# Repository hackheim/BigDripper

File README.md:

# Big Dripper 

### BigDripper – Controller Board and Operating Principle

BigDripper is Hackheim’s version of the classic bicycle-mounted water printer (see links below). The printer is being developed as a community project, with the goal of having it completed by the end of September 2026.

The printer consists of 16 solenoid valves mounted in a row across the bicycle trailer. The valves are supplied with water from a tank and pump. When a valve is opened briefly, it releases a small amount of water onto the ground, forming a single pixel. Together, the 16 valves produce one vertical column of 16 pixels. As the bicycle moves forward and new columns are printed in sequence, the trailer effectively operates as a large-scale dot-matrix printer.

An encoder measures the distance travelled by the bicycle. Rather than advancing through the image at fixed time intervals, the controller selects the next column after the bicycle has travelled a predefined distance. This helps maintain the proportions of the printed text or graphics even when the cycling speed varies.

### Controller board

The controller is based on an ESP32-S3 DevKitC-1, which plugs into a custom-designed carrier board. To make the board easy to maintain and repair—and also suitable for educational use and soldering workshops—we have chosen to use through-hole components throughout the carrier board.

The board has a nominal input voltage of 12 V, which is also the operating voltage of the solenoid valves. A TL2575-based switching regulator generates 5 V for the ESP32 development board and the other logic circuitry.

The regulator itself supports an input voltage of up to 40 V. However, the input voltage is also supplied directly to the solenoid valves. When using a voltage higher than 12 V, both the valves and all other components connected to the input-voltage rail must therefore be rated for the selected voltage.

### Solenoid valve control

The 16 valve outputs are controlled by IRL540N MOSFETs in a low-side switching configuration. The control signals from the ESP32 use 3.3 V logic and are therefore routed through SN74HCT125NE4 buffers powered from 5 V. These buffers provide logic-level translation and drive the MOSFET gates at a higher and more suitable voltage.

Each MOSFET gate is connected to its buffer output through a 33-ohm series resistor. The control signals also have 47-kilohm pull-down resistors, ensuring that the valves remain switched off while the ESP32 is starting, being reset, or not actively driving the outputs.

Each valve output is protected by a dedicated 1N4007 flyback diode. The diode suppresses the inductive voltage spike generated when the current through the solenoid coil is interrupted, protecting the MOSFET from excessive drain voltage.

### Connections and expansion options

The board has a dedicated input for an encoder with transistor outputs and A/B signals. An additional header provides access to 12 spare GPIO signals, together with 3.3 V, 5 V, and ground connections.

Four separate outputs are available for NeoPixel LEDs. These signals are also level-shifted from 3.3 V to 5 V using an SN74HCT125 buffer, and each data output includes a 330-ohm series resistor.

The board also includes indicator LEDs for the 12 V, 5 V, and 3.3 V supply rails, making it easy to verify that the different supply voltages are present.

All external inputs and outputs use WAGO board-to-wire lever connectors, allowing wires to be connected and removed easily without tools.

### Schematic

[schematic](./hardware/pdf/schematic.pdf)

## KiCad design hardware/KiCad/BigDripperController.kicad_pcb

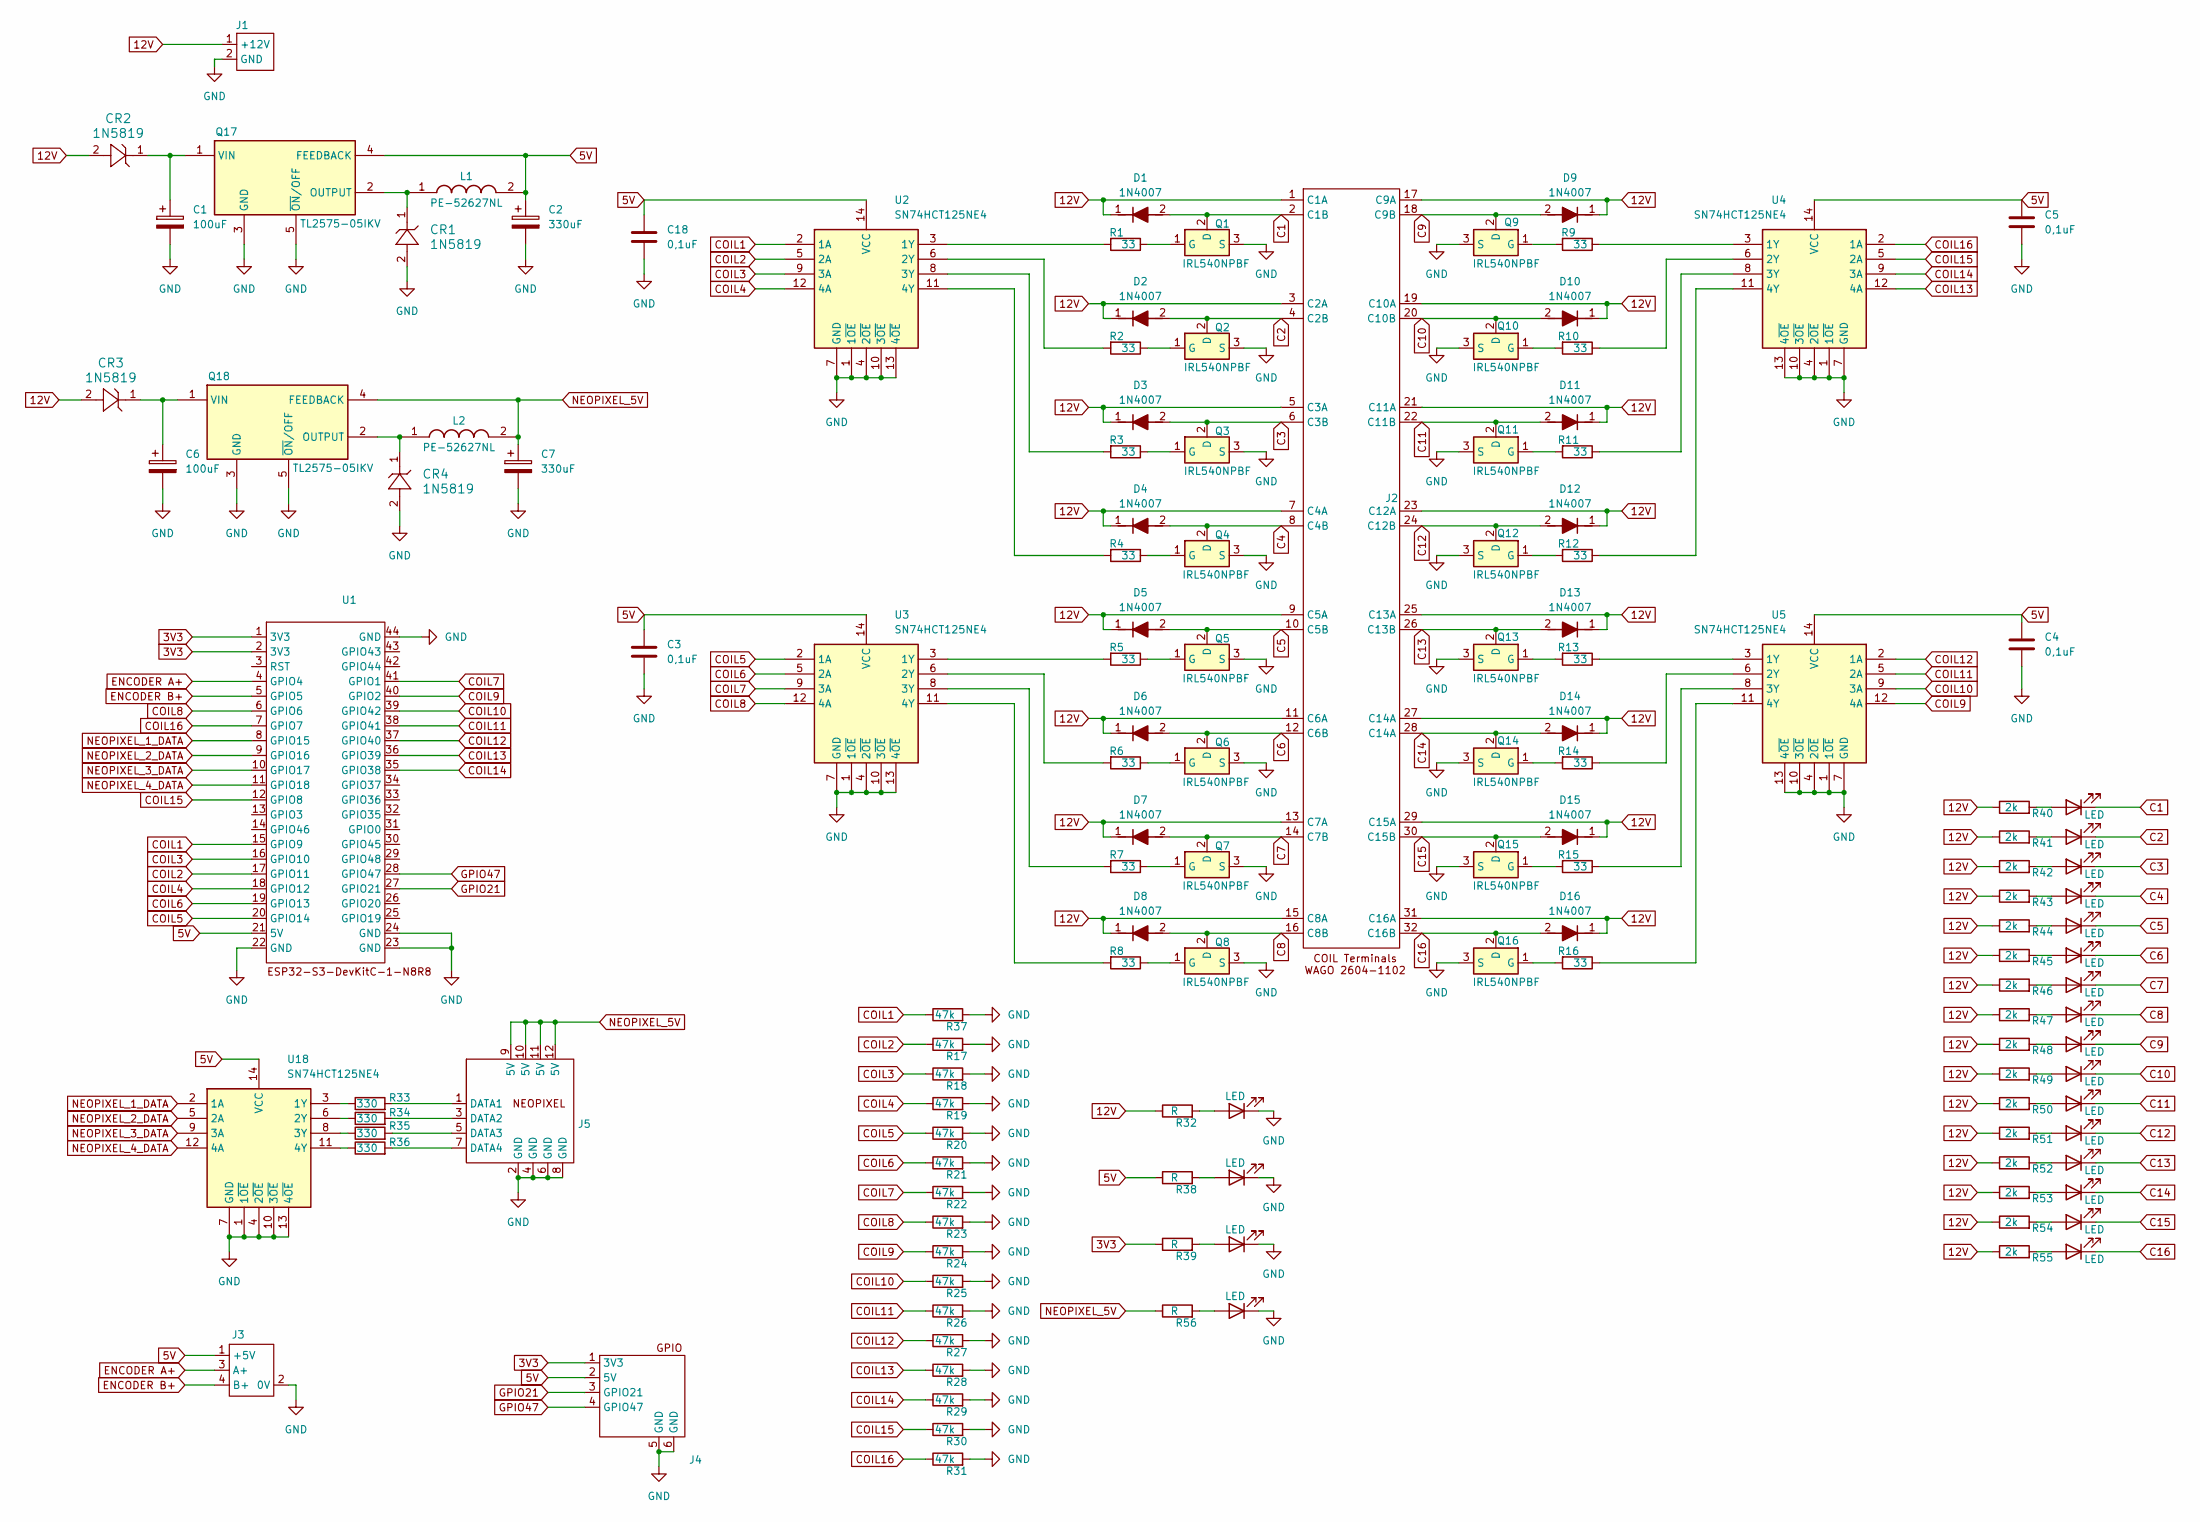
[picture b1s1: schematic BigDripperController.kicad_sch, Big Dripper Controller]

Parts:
C1, C6: 100uF; CAP ALUM 10UF 20% 25V RADIAL TH - WÜRTH - 860020472003
C2, C7: 330uF; CAP ALUM 10UF 20% 25V RADIAL TH - WÜRTH - 860020472003
C3, C4, C5, C18: 0,1uF; CAP0,1uF_K104K15X7RF5TH5V
CR1, CR2, CR3, CR4: 1N5819; DO-41_STM
D1, D2, D3, D4, D5, D6, D7, D8, D9, D10, D11, D12, D13, D14, D15, D16: 1N4007; Mouser Part Number 637-1N4007
D17, D18, D19, D20, D21, D22, D23, D24, D25, D26, D27, D28, D29, D30, D31, D32, D33, D34, D35, D36: LED; LED_D5.0mm
J1: BigDripperPowerConnector-WAGO2604-1102
J2: BigDripperCoilConnector-WAGO2604-1102
J3: BigDripperEncoderConnector-WAGO2604-1102
J4: BigDripperGPIOConnector-WAGO2604-1102
J5: BigDripperNeopixelConnector-WAGO2604-1102
L1, L2: PE-52627NL; PE52627NL; Mouser Part Number 673-PE-52627NL
Q1, Q2, Q3, Q4, Q5, Q6, Q7, Q8, Q9, Q10, Q11, Q12, Q13, Q14, Q15, Q16: IRL540NPBF; Mouser Part Number 942-IRL540NPBF
Q17, Q18: TL2575-05IKV; Mouser Part Number 595-TL2575-05IKV
R1, R2, R3, R4, R5, R6, R7, R8, R9, R10, R11, R12, R13, R14, R15, R16: 33; R_Axial_DIN0207_L6.3mm_D2.5mm_P10.16mm_Horizontal
R17, R18, R19, R20, R21, R22, R23, R24, R25, R26, R27, R28, R29, R30, R31, R37: 47k; R_Axial_DIN0207_L6.3mm_D2.5mm_P10.16mm_Horizontal
R32, R38, R39, R56: R; R_Axial_DIN0207_L6.3mm_D2.5mm_P10.16mm_Horizontal
R33, R34, R35, R36: 330; R_Axial_DIN0207_L6.3mm_D2.5mm_P10.16mm_Horizontal
R40, R41, R42, R43, R44, R45, R46, R47, R48, R49, R50, R51, R52, R53, R54, R55: 2k; R_Axial_DIN0207_L6.3mm_D2.5mm_P10.16mm_Horizontal
U1: ESP32-S3-DevKitC-1-N8R8
U2, U3, U4, U5, U18: SN74HCT125NE4; DIP14; Mouser Part Number 595-SN74HCT125NE4

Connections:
3V3: J4.1 (3V3), R39.1, U1.1 (3V3), U1.2 (3V3)
5V: C2.1, C3.1, C4.1, C5.1, C18.1, J3.1 (+5V), J4.2 (5V), L1.2 (1-), Q17.4 (FEEDBACK), R38.1, U1.21 (5V), U2.14 (VCC), U3.14 (VCC), U4.14 (VCC), U5.14 (VCC), U18.14 (VCC)
12V: CR2.2, CR3.2, D1.1 (K), D2.1 (K), D3.1 (K), D4.1 (K), D5.1 (K), D6.1 (K), D7.1 (K), D8.1 (K), D9.1 (K), D10.1 (K), D11.1 (K), D12.1 (K), D13.1 (K), D14.1 (K), D15.1 (K), D16.1 (K), J1.1 (+12V), J2.1 (C1A), J2.3 (C2A), J2.5 (C3A), J2.7 (C4A), J2.9 (C5A), J2.11 (C6A), J2.13 (C7A), J2.15 (C8A), J2.17 (C9A), J2.19 (C10A), J2.21 (C11A), J2.23 (C12A), J2.25 (C13A), J2.27 (C14A), J2.29 (C15A), J2.31 (C16A), R32.1, R40.1, R41.1, R42.1, R43.1, R44.1, R45.1, R46.1, R47.1, R48.1, R49.1, R50.1, R51.1, R52.1, R53.1, R54.1, R55.1
C1: D1.2 (A), D20.1 (K), J2.2 (C1B), Q1.2 (D)
C2: D2.2 (A), D21.1 (K), J2.4 (C2B), Q2.2 (D)
C3: D3.2 (A), D22.1 (K), J2.6 (C3B), Q3.2 (D)
C4: D4.2 (A), D23.1 (K), J2.8 (C4B), Q4.2 (D)
C5: D5.2 (A), D24.1 (K), J2.10 (C5B), Q5.2 (D)
C6: D6.2 (A), D25.1 (K), J2.12 (C6B), Q6.2 (D)
C7: D7.2 (A), D26.1 (K), J2.14 (C7B), Q7.2 (D)
C8: D8.2 (A), D27.1 (K), J2.16 (C8B), Q8.2 (D)
C9: D9.2 (A), D28.1 (K), J2.18 (C9B), Q9.2 (D)
C10: D10.2 (A), D29.1 (K), J2.20 (C10B), Q10.2 (D)
C11: D11.2 (A), D30.1 (K), J2.22 (C11B), Q11.2 (D)
C12: D12.2 (A), D31.1 (K), J2.24 (C12B), Q12.2 (D)
C13: D13.2 (A), D32.1 (K), J2.26 (C13B), Q13.2 (D)
C14: D14.2 (A), D33.1 (K), J2.28 (C14A), Q14.2 (D)
C15: D15.2 (A), D34.1 (K), J2.30 (C15B), Q15.2 (D)
C16: D16.2 (A), D35.1 (K), J2.32 (C16B), Q16.2 (D)
COIL1: R37.1, U1.15 (GPIO9), U2.2 (1A)
COIL2: R17.1, U1.17 (GPIO11), U2.5 (2A)
COIL3: R18.1, U1.16 (GPIO10), U2.9 (3A)
COIL4: R19.1, U1.18 (GPIO12), U2.12 (4A)
COIL5: R20.1, U1.20 (GPIO14), U3.2 (1A)
COIL6: R21.1, U1.19 (GPIO13), U3.5 (2A)
COIL7: R22.1, U1.41 (GPIO1), U3.9 (3A)
COIL8: R23.1, U1.6 (GPIO6), U3.12 (4A)
COIL9: R24.1, U1.40 (GPIO2), U5.12 (4A)
COIL10: R25.1, U1.39 (GPIO42), U5.9 (3A)
COIL11: R26.1, U1.38 (GPIO41), U5.5 (2A)
COIL12: R27.1, U1.37 (GPIO40), U5.2 (1A)
COIL13: R28.1, U1.36 (GPIO39), U4.12 (4A)
COIL14: R29.1, U1.35 (GPIO38), U4.9 (3A)
COIL15: R30.1, U1.12 (GPIO8), U4.5 (2A)
COIL16: R31.1, U1.7 (GPIO7), U4.2 (1A)
ENCODER A+: J3.3 (A+), U1.4 (GPIO4)
ENCODER B+: J3.4 (B+), U1.5 (GPIO5)
GND: C1.2, C2.2, C3.2, C4.2, C5.2, C6.2, C7.2, C18.2, CR1.2, CR4.2, D17.1 (K), D18.1 (K), D19.1 (K), D36.1 (K), J1.2 (GND), J3.2 (0V), J4.5 (GND), J4.6 (GND), J5.2 (GND), J5.4 (GND), J5.6 (GND), J5.8 (GND), Q1.3 (S), Q2.3 (S), Q3.3 (S), Q4.3 (S), Q5.3 (S), Q6.3 (S), Q7.3 (S), Q8.3 (S), Q9.3 (S), Q10.3 (S), Q11.3 (S), Q12.3 (S), Q13.3 (S), Q14.3 (S), Q15.3 (S), Q16.3 (S), Q17.3 (GND), Q17.5 (~ON/OFF), Q18.3 (GND), Q18.5 (~ON/OFF), R17.2, R18.2, R19.2, R20.2, R21.2, R22.2, R23.2, R24.2, R25.2, R26.2, R27.2, R28.2, R29.2, R30.2, R31.2, R37.2, U1.22 (GND), U1.23 (GND), U1.24 (GND), U1.44 (GND), U2.1 (1~OE), U2.4 (2~OE), U2.7 (GND), U2.10 (3~OE), U2.13 (4~OE), U3.1 (1~OE), U3.4 (2~OE), U3.7 (GND), U3.10 (3~OE), U3.13 (4~OE), U4.1 (1~OE), U4.4 (2~OE), U4.7 (GND), U4.10 (3~OE), U4.13 (4~OE), U5.1 (1~OE), U5.4 (2~OE), U5.7 (GND), U5.10 (3~OE), U5.13 (4~OE), U18.1 (1~OE), U18.4 (2~OE), U18.7 (GND), U18.10 (3~OE), U18.13 (4~OE)
GPIO21: J4.3 (GPIO21), U1.27 (GPIO21)
GPIO47: J4.4 (GPIO47), U1.28 (GPIO47)
NEOPIXEL_1_DATA: U1.8 (GPIO15), U18.2 (1A)
NEOPIXEL_2_DATA: U1.9 (GPIO16), U18.5 (2A)
NEOPIXEL_3_DATA: U1.10 (GPIO17), U18.9 (3A)
NEOPIXEL_4_DATA: U1.11 (GPIO18), U18.12 (4A)
NEOPIXEL_5V: C7.1, J5.9 (5V), J5.10 (5V), J5.11 (5V), J5.12 (5V), L2.2 (1-), Q18.4 (FEEDBACK), R56.1
unnamed: D17.2 (A), R32.2
unnamed: D18.2 (A), R38.2
unnamed: D19.2 (A), R39.2
unnamed: D20.2 (A), R40.2
unnamed: D21.2 (A), R41.2
unnamed: D22.2 (A), R42.2
unnamed: D23.2 (A), R43.2
unnamed: D24.2 (A), R44.2
unnamed: D25.2 (A), R45.2
unnamed: D26.2 (A), R46.2
unnamed: D27.2 (A), R47.2
unnamed: D28.2 (A), R48.2
unnamed: D29.2 (A), R49.2
unnamed: D30.2 (A), R50.2
unnamed: D31.2 (A), R51.2
unnamed: D32.2 (A), R52.2
unnamed: D33.2 (A), R53.2
unnamed: D34.2 (A), R54.2
unnamed: D35.2 (A), R55.2
unnamed: D36.2 (A), R56.2
unnamed: J5.1 (DATA1), R33.2
unnamed: J5.3 (DATA2), R34.2
unnamed: J5.5 (DATA3), R35.2
unnamed: J5.7 (DATA4), R36.2
unnamed: CR1.1, L1.1 (1+), Q17.2 (OUTPUT)
unnamed: CR4.1, L2.1 (1+), Q18.2 (OUTPUT)
unnamed: Q1.1 (G), R1.1
unnamed: Q2.1 (G), R2.1
unnamed: Q3.1 (G), R3.1
unnamed: Q4.1 (G), R4.1
unnamed: Q5.1 (G), R5.1
unnamed: Q6.1 (G), R6.1
unnamed: Q7.1 (G), R7.1
unnamed: Q8.1 (G), R8.1
unnamed: Q9.1 (G), R9.2
unnamed: Q10.1 (G), R10.2
unnamed: Q11.1 (G), R11.2
unnamed: Q12.1 (G), R12.2
unnamed: Q13.1 (G), R13.2
unnamed: Q14.1 (G), R14.2
unnamed: Q15.1 (G), R15.2
unnamed: Q16.1 (G), R16.2
unnamed: C1.1, CR2.1, Q17.1 (VIN)
unnamed: C6.1, CR3.1, Q18.1 (VIN)
unnamed: R1.2, U2.3 (1Y)
unnamed: R2.2, U2.6 (2Y)
unnamed: R3.2, U2.8 (3Y)
unnamed: R4.2, U2.11 (4Y)
unnamed: R5.2, U3.3 (1Y)
unnamed: R6.2, U3.6 (2Y)
unnamed: R7.2, U3.8 (3Y)
unnamed: R8.2, U3.11 (4Y)
unnamed: R9.1, U4.3 (1Y)
unnamed: R10.1, U4.6 (2Y)
unnamed: R11.1, U4.8 (3Y)
unnamed: R12.1, U4.11 (4Y)
unnamed: R13.1, U5.3 (1Y)
unnamed: R14.1, U5.6 (2Y)
unnamed: R15.1, U5.8 (3Y)
unnamed: R16.1, U5.11 (4Y)
unnamed: R33.1, U18.3 (1Y)
unnamed: R34.1, U18.6 (2Y)
unnamed: R35.1, U18.8 (3Y)
unnamed: R36.1, U18.11 (4Y)

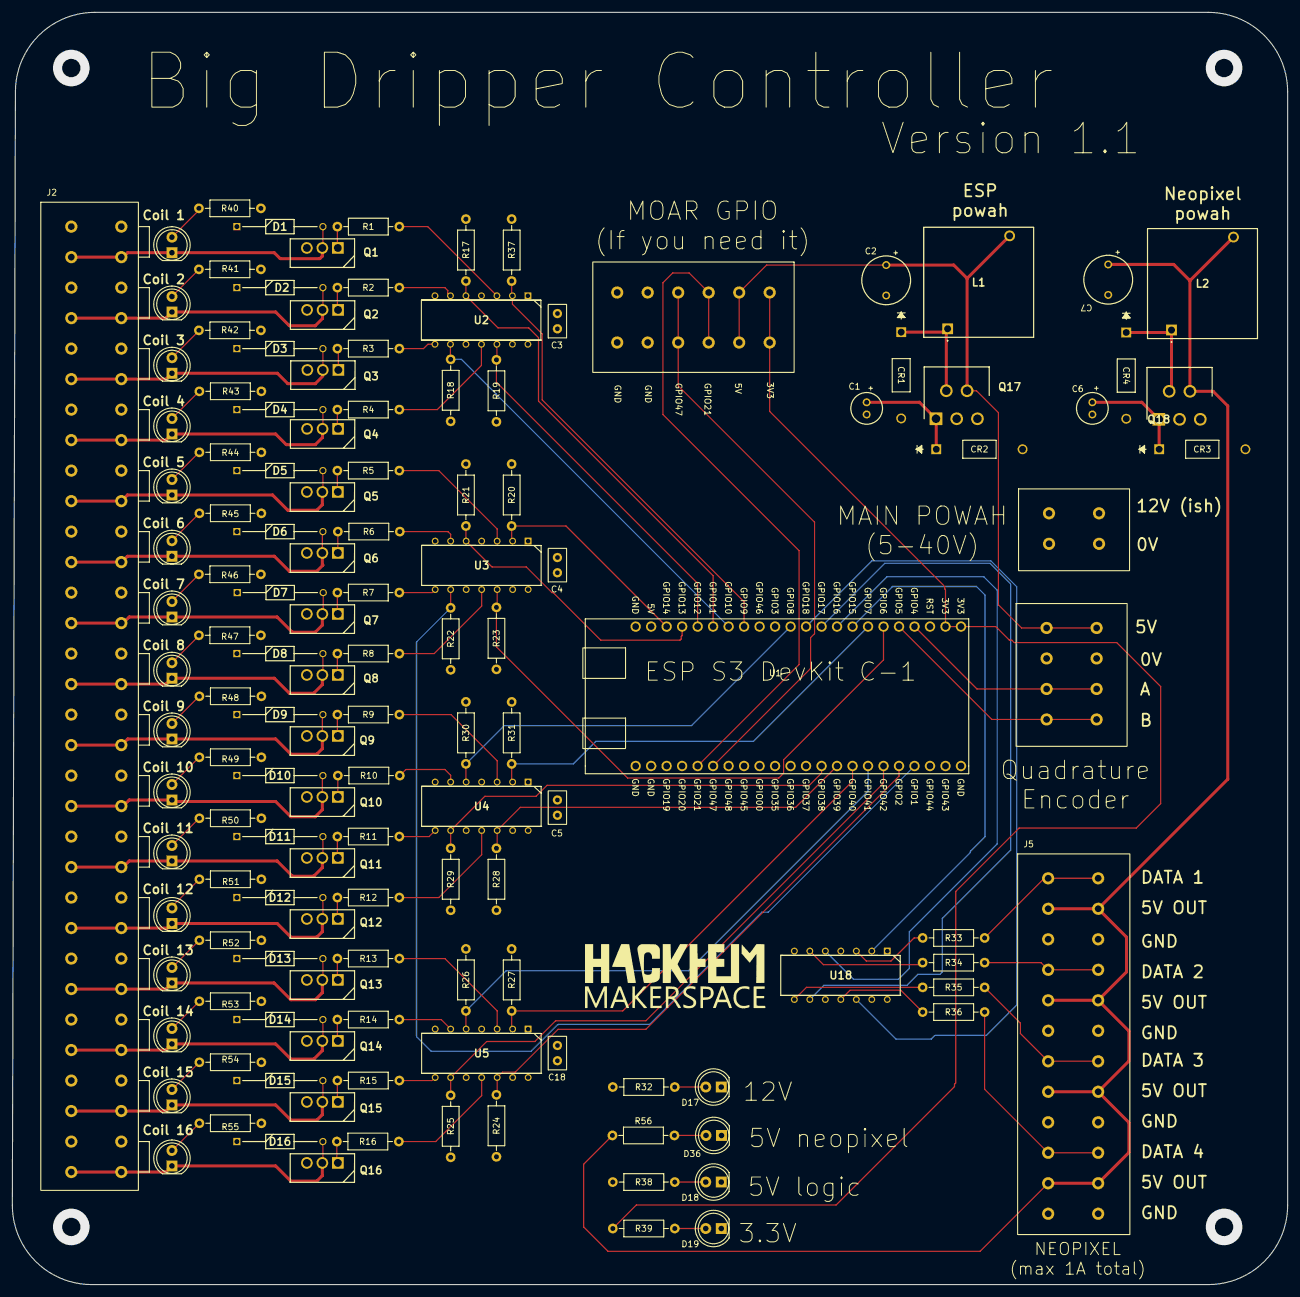
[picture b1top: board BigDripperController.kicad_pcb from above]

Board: 4 copper layers, 209.1 x 208.6 mm, 135 parts (0 on the bottom side), 109 nets.
